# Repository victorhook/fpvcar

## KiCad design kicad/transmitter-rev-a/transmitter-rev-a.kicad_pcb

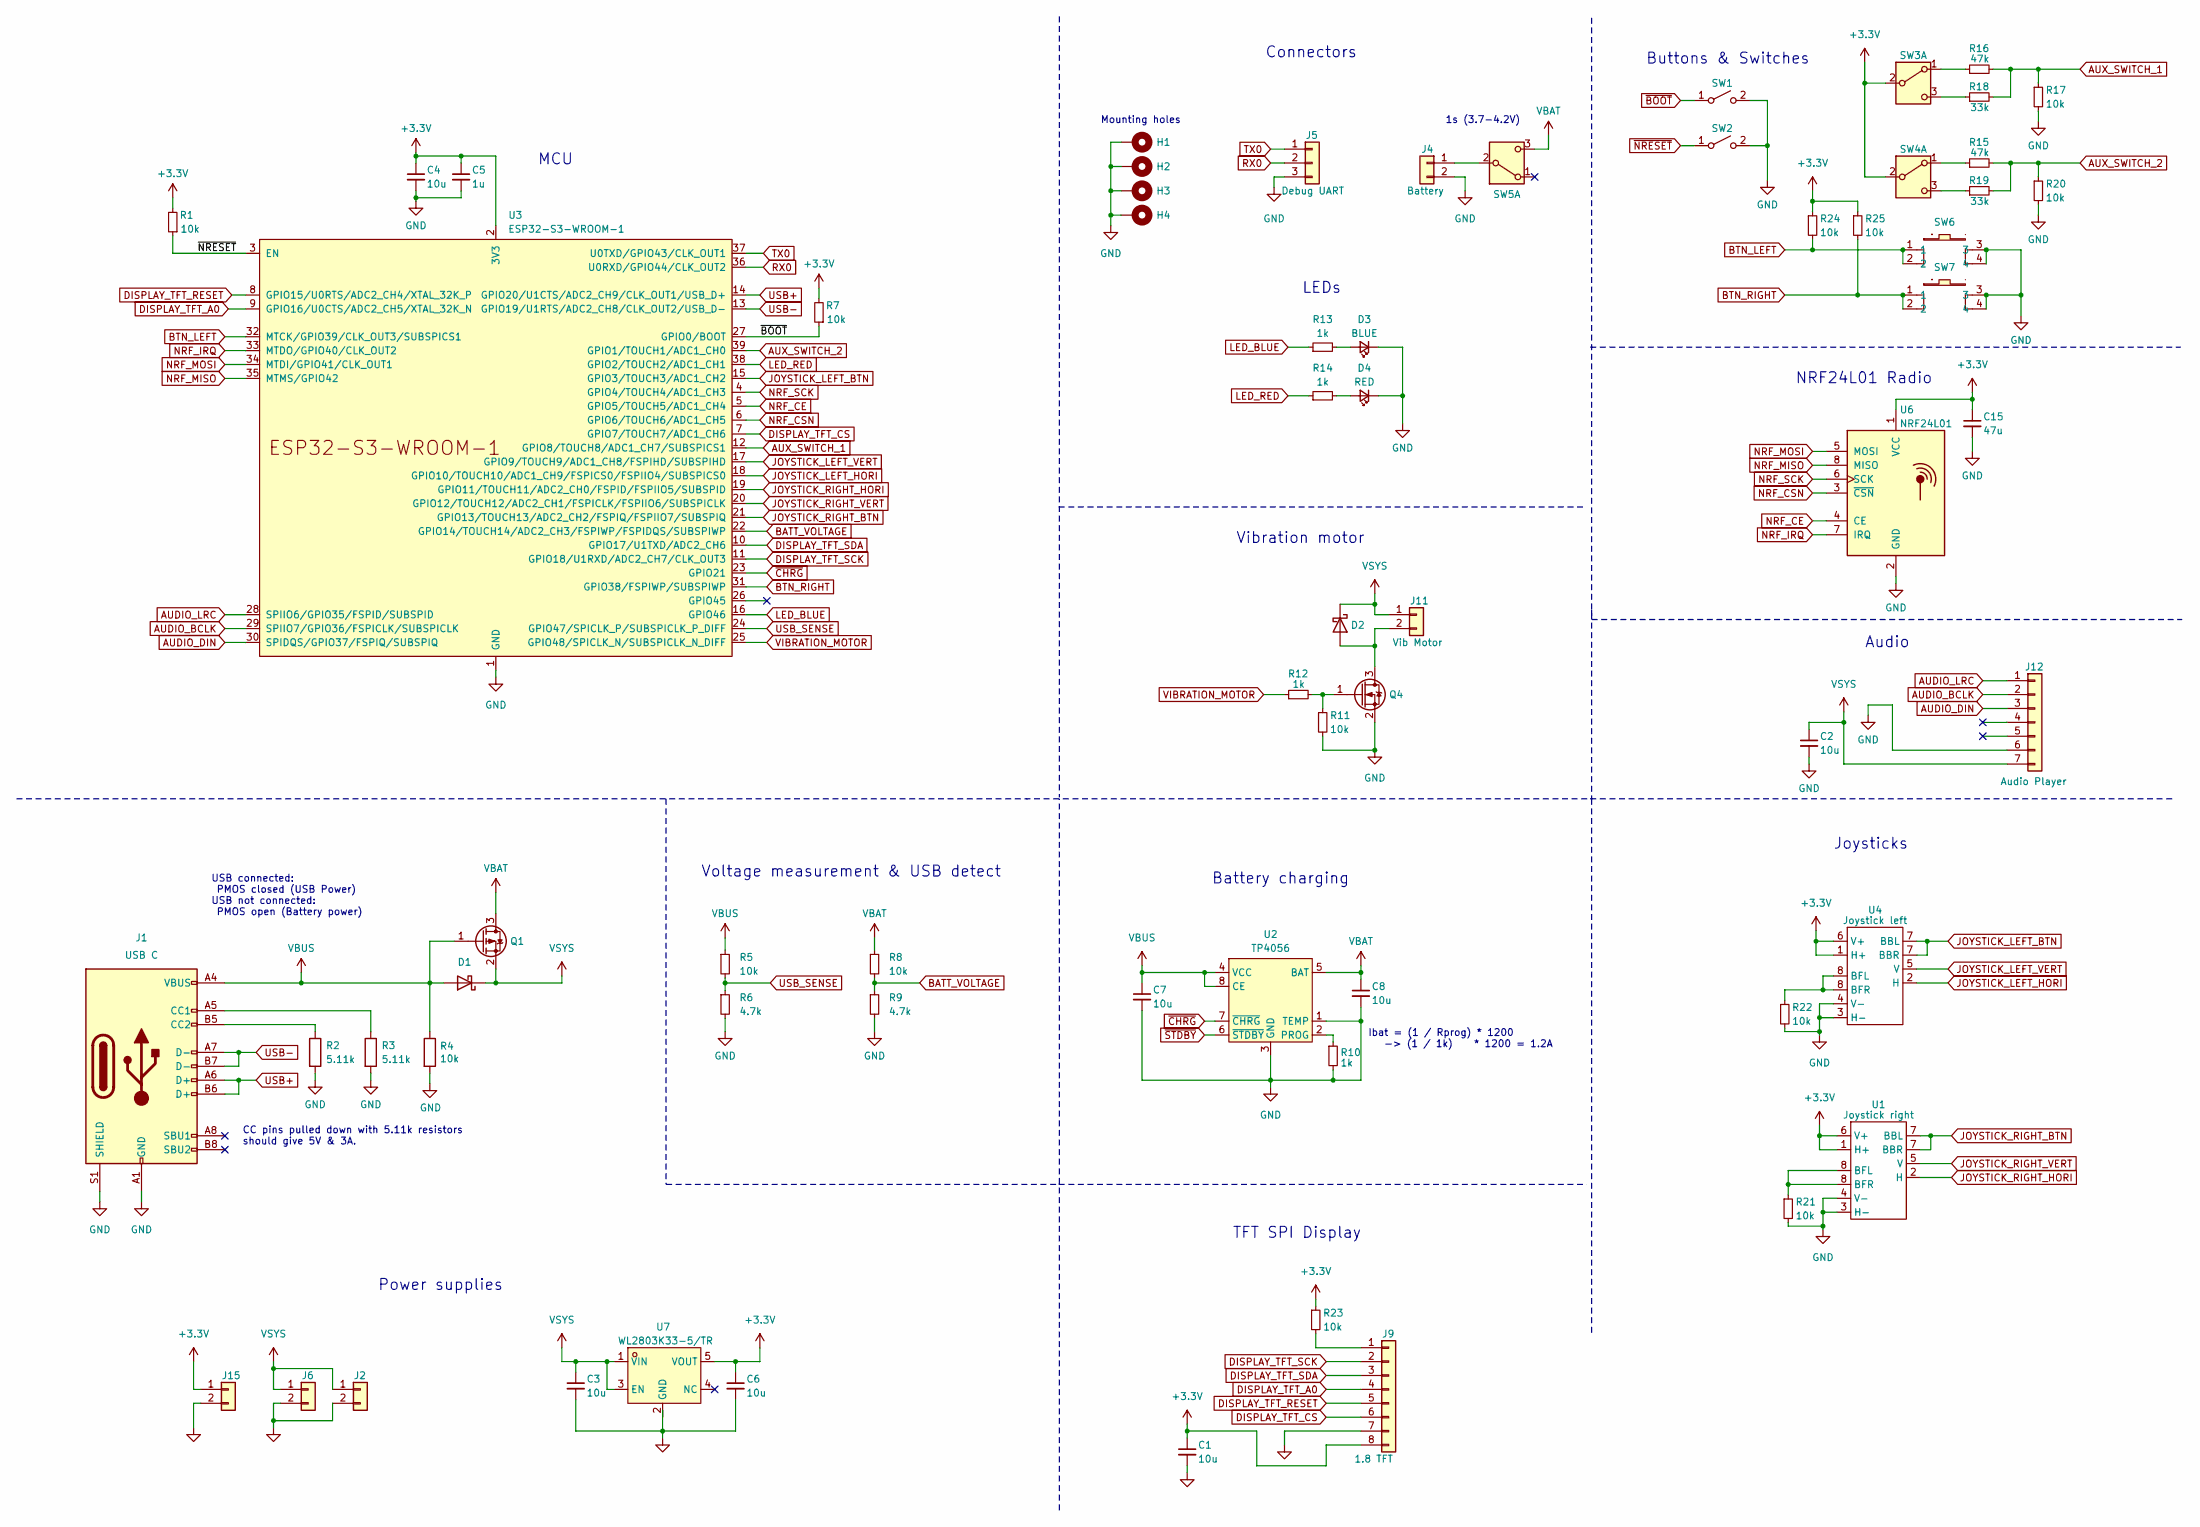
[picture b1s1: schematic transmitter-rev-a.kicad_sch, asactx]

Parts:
C1, C2, C3, C4, C6, C7, C8: 10u; C_0603_1608Metric
C5: 1u; C_0402_1005Metric
C15: 47u; C_1206_3216Metric
D1: D_Schottky; D_SOD-123
D2: D_Schottky; D_SOD-323
D3: BLUE; LED_0603_1608Metric
D4: RED; LED_0603_1608Metric
H1, H2, H3, H4: MountingHole_Pad; MountingHole_3.2mm_M3_Pad_Via
J1: USB C; USB-SMD_GT-USB-7010AN
J2, J6, J15: VSYS_VOLTAGE; Conn_01x02_no_Silk
J4: Battery; PinSocket_1x02_P2.54mm_Vertical
J5: Debug UART; PinSocket_1x03_P2.54mm_Vertical
J9: 1.8 TFT; PinSocket_1x08_P2.54mm_Vertical
J11: Vib Motor; Conn_01x02_no_Silk
J12: Audio Player; PinSocket_1x07_P2.54mm_Vertical
Q1: Q_PMOS_GSD; SOT-23
Q4: Q_NMOS_Depletion_GSD; SOT-23
R1, R4, R5, R7, R8, R11, R17, R20, R21, R22, R23, R24, R25: 10k; R_0402_1005Metric
R2, R3: 5.11k; R_0402_1005Metric
R6, R9: 4.7k; R_0402_1005Metric
R10, R12, R13, R14: 1k; R_0402_1005Metric
R15, R16: 47k; R_0402_1005Metric
R18, R19: 33k; R_0402_1005Metric
SW1, SW2: SW_SPST; SW-SMD_L4.0-W2.9-LS5.0
SW3: SWITCH 1; On-Off-On_Switch
SW4: SWITCH 2; On-Off-On_Switch
SW5: Battery; SideSwitch_5_Legs
SW6, SW7: KAN0641-0431B-L; KEY-SMD_4P-L6.0-W6.0-P4.50-LS10.0; LCSC Part C231670
U1: Joystick right; PS4tJoystick
U2: TP4056; ESOP-8_L4.9-W3.9-P1.27-LS6.0-BL-EP; LCSC Part C725790
U3: ESP32-S3-WROOM-1
U4: Joystick left; PS4tJoystick
U6: NRF24L01; PinSocket_2x04_P2.54mm_Vertical
U7: WL2803K33-5/TR; SOT-89-5; LCSC Part C192927

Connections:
+3.3V: C1.1, C4.1, C5.1, C6.1, C15.1, J9.8, J15.1, R1.2, R7.2, R23.1, R24.1, R25.1, SW3.2 (B), SW4.2 (B), U1.1 (H+), U1.6 (V+), U3.2 (3V3), U4.1 (H+), U4.6 (V+), U6.1 (VCC), U7.5 (VOUT)
AUDIO_BCLK: J12.2, U3.29 (SPIIO7/GPIO36/FSPICLK/SUBSPICLK)
AUDIO_DIN: J12.3, U3.30 (SPIDQS/GPIO37/FSPIQ/SUBSPIQ)
AUDIO_LRC: J12.1, U3.28 (SPIIO6/GPIO35/FSPID/SUBSPID)
AUX_SWITCH_1: R16.2, R17.1, R18.2, U3.12 (GPIO8/TOUCH8/ADC1_CH7/SUBSPICS1)
AUX_SWITCH_2: R15.2, R19.2, R20.1, U3.39 (GPIO1/TOUCH1/ADC1_CH0)
BATT_VOLTAGE: R8.2, R9.1, U3.22 (GPIO14/TOUCH14/ADC2_CH3/FSPIWP/FSPIDQS/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)
BTN_LEFT: R24.2, SW6.1, SW6.2, U3.32 (MTCK/GPIO39/CLK_OUT3/SUBSPICS1)
BTN_RIGHT: R25.2, SW7.1, SW7.2, U3.31 (GPIO38/FSPIWP/SUBSPIWP)
DISPLAY_TFT_A0: J9.4, U3.9 (GPIO16/U0CTS/ADC2_CH5/XTAL_32K_N)
DISPLAY_TFT_CS: J9.6, U3.7 (GPIO7/TOUCH7/ADC1_CH6)
DISPLAY_TFT_RESET: J9.5, U3.8 (GPIO15/U0RTS/ADC2_CH4/XTAL_32K_P)
DISPLAY_TFT_SCK: J9.2, U3.11 (GPIO18/U1RXD/ADC2_CH7/CLK_OUT3)
DISPLAY_TFT_SDA: J9.3, U3.10 (GPIO17/U1TXD/ADC2_CH6)
GND: C1.2, C2.2, C3.2, C4.2, C5.2, C6.2, C7.2, C8.2, C15.2, D3.1 (K), D4.1 (K), H1.1, H2.1, H3.1, H4.1, J1.A1 (GND), J1.A12 (GND), J1.B1 (GND), J1.B12 (GND), J1.S1 (SHIELD), J2.2, J4.2, J5.3, J6.2, J9.7, J12.6, J15.2, Q4.2 (S), R2.2, R3.2, R4.2, R6.2, R9.2, R10.2, R11.2, R17.2, R20.2, R21.2, R22.2, SW1.2 (B), SW2.2 (B), SW6.3, SW6.4, SW7.3, SW7.4, U1.3 (H-), U1.4 (V-), U2.1 (TEMP), U2.3 (GND), U3.1 (GND), U3.40 (GND), U3.41 (GND), U4.3 (H-), U4.4 (V-), U6.2 (GND)
JOYSTICK_LEFT_BTN: U3.15 (GPIO3/TOUCH3/ADC1_CH2), U4.7 (BBL)
JOYSTICK_LEFT_HORI: U3.18 (GPIO10/TOUCH10/ADC1_CH9/FSPICS0/FSPIIO4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), U4.2 (H)
JOYSTICK_LEFT_VERT: U3.17 (GPIO9/TOUCH9/ADC1_CH8/FSPIHD/SUBSPIHD), U4.5 (V)
JOYSTICK_RIGHT_BTN: U1.7 (BBL), U3.21 (GPIO13/TOUCH13/ADC2_CH2/FSPIQ/FSPIIO7/S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)
JOYSTICK_RIGHT_HORI: U1.2 (H), U3.19 (GPIO11/TOUCH11/ADC2_CH0/FSPID/FSPIIO5/S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)
JOYSTICK_RIGHT_VERT: U1.5 (V), U3.20 (GPIO12/TOUCH12/ADC2_CH1/FSPICLK/FSPIIO6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)
LED_BLUE: R13.1, U3.16 (GPIO46)
LED_RED: R14.1, U3.38 (GPIO2/TOUCH2/ADC1_CH1)
NRF_CE: U3.5 (GPIO5/TOUCH5/ADC1_CH4), U6.4 (CE)
NRF_CSN: U3.6 (GPIO6/TOUCH6/ADC1_CH5), U6.3 (~CSN)
NRF_IRQ: U3.33 (MTDO/GPIO40/CLK_OUT2), U6.7 (IRQ)
NRF_MISO: U3.35 (MTMS/GPIO42), U6.8 (MISO)
NRF_MOSI: U3.34 (MTDI/GPIO41/CLK_OUT1), U6.5 (MOSI)
NRF_SCK: U3.4 (GPIO4/TOUCH4/ADC1_CH3), U6.6 (SCK)
unnamed: D2.2 (A), J11.2, Q4.3 (D)
unnamed: D3.2 (A), R13.2
unnamed: D4.2 (A), R14.2
unnamed: J1.A5 (CC1), R3.1
unnamed: J1.B5 (CC2), R2.1
unnamed: J4.1, SW5.2 (B)
unnamed: J9.1, R23.2
unnamed: Q4.1 (G), R11.1, R12.2
unnamed: R16.1, SW3.1 (A)
unnamed: R18.1, SW3.3 (C)
unnamed: R15.1, SW4.1 (A)
unnamed: R19.1, SW4.3 (C)
unnamed: R21.1, U1.8 (BFL)
unnamed: R10.1, U2.2 (PROG)
unnamed: R22.1, U4.8 (BFL)
RX0: J5.2, U3.36 (U0RXD/GPIO44/CLK_OUT2)
TX0: J5.1, U3.37 (U0TXD/GPIO43/CLK_OUT1)
USB+: J1.A6 (D+), J1.B6 (D+), U3.14 (GPIO20/U1CTS/ADC2_CH9/CLK_OUT1/USB_D+)
USB-: J1.A7 (D-), J1.B7 (D-), U3.13 (GPIO19/U1RTS/ADC2_CH8/CLK_OUT2/USB_D-)
USB_SENSE: R5.2, R6.1, U3.24 (GPIO47/SPICLK_P/SUBSPICLK_P_DIFF)
VBAT: C8.1, Q1.3 (D), R8.1, SW5.3 (C), U2.5 (BAT)
VBUS: C7.1, D1.2 (A), J1.A4 (VBUS), J1.A9 (VBUS), J1.B4 (VBUS), J1.B9 (VBUS), Q1.1 (G), R4.1, R5.1, U2.4 (VCC), U2.8 (CE)
VIBRATION_MOTOR: R12.1, U3.25 (GPIO48/SPICLK_N/SUBSPICLK_N_DIFF)
VSYS: C2.1, C3.1, D1.1 (K), D2.1 (K), J2.1, J6.1, J11.1, J12.7, Q1.2 (S), U7.1 (VIN), U7.3 (EN)
~BOOT: R7.1, SW1.1 (A), U3.27 (GPIO0/BOOT)
~CHRG: U2.7 (~CHRG), U3.23 (GPIO21)
~NRESET: R1.1, SW2.1 (A), U3.3 (EN)
~STDBY: U2.6 (~STDBY)

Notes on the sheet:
Vibration motor
TFT SPI Display
MCU
Audio
LEDs
Ibat = (1 / Rprog) * 1200 -> (1 / 1k) * 1200 = 1.2A
NRF24L01 Radio
CC pins pulled down with 5.11k resistors should give 5V & 3A.
USB connected: PMOS closed (USB Power) USB not connected: PMOS open (Battery power)
Voltage measurement & USB detect
Connectors
Buttons & Switches
Joysticks
Power supplies
Battery charging
1s (3.7-4.2V)
Mounting holes

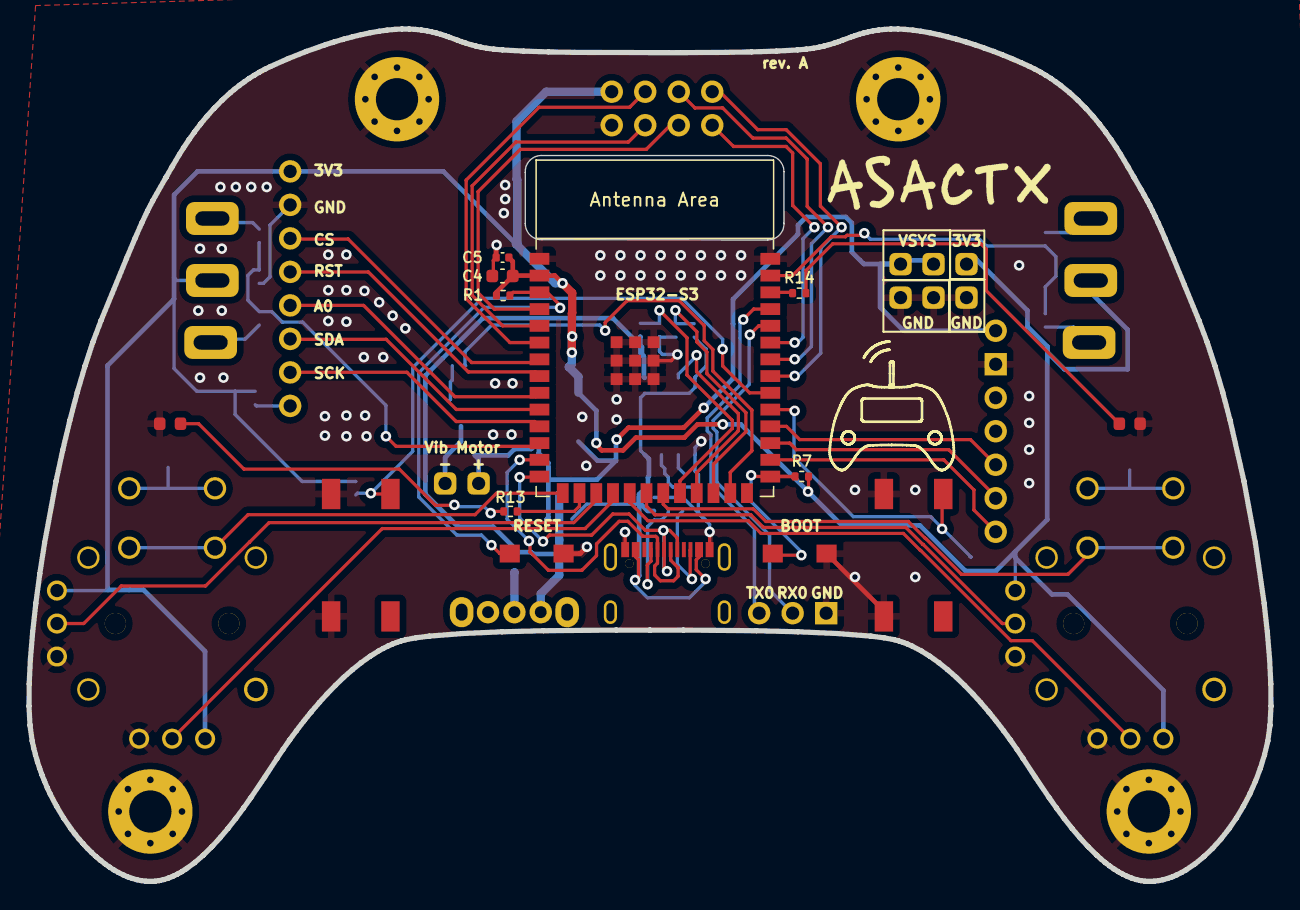
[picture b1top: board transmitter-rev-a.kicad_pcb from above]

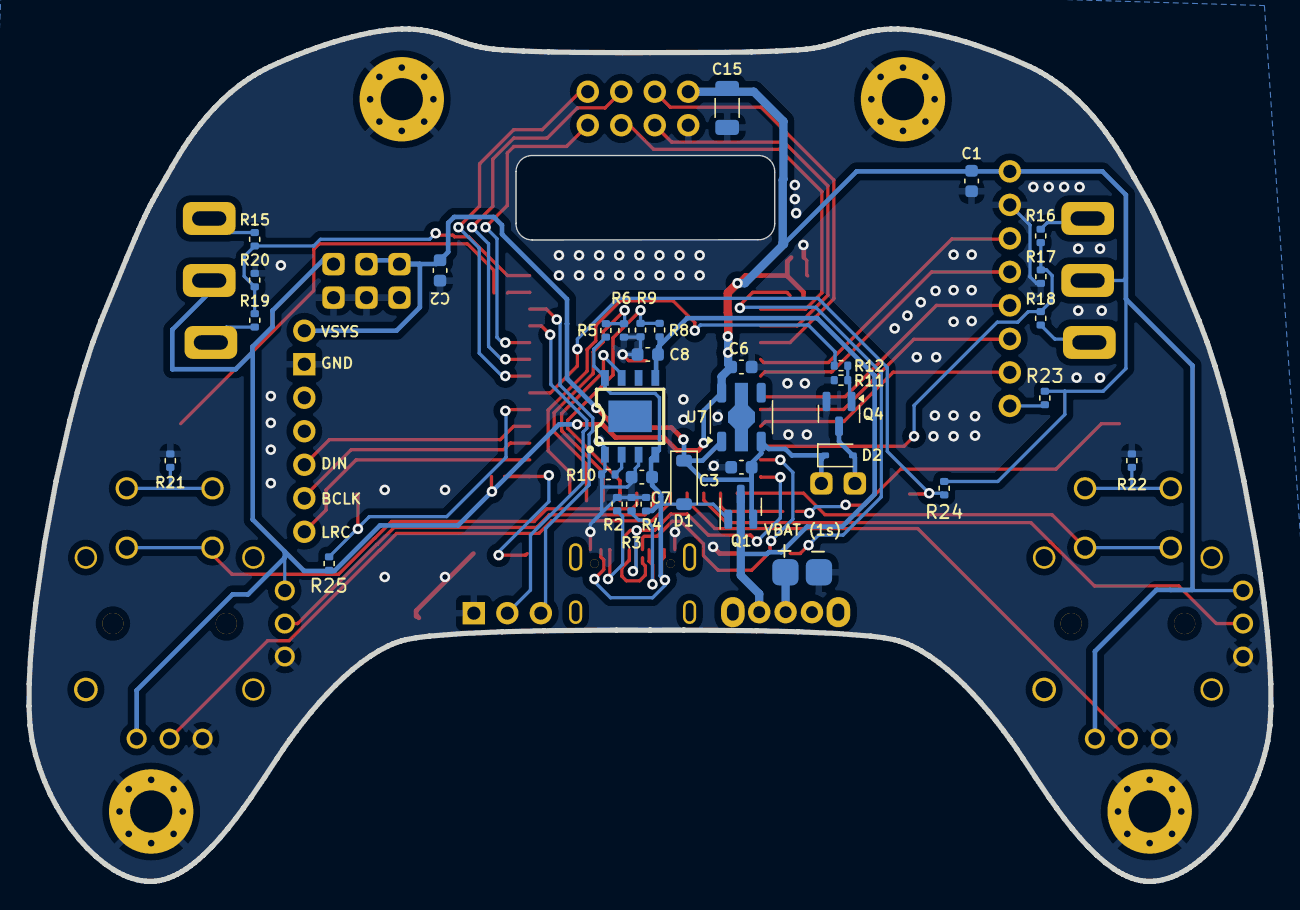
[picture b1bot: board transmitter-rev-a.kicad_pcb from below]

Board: 2 copper layers, 94.2 x 64.6 mm, 66 parts (35 on the bottom side), 56 nets.

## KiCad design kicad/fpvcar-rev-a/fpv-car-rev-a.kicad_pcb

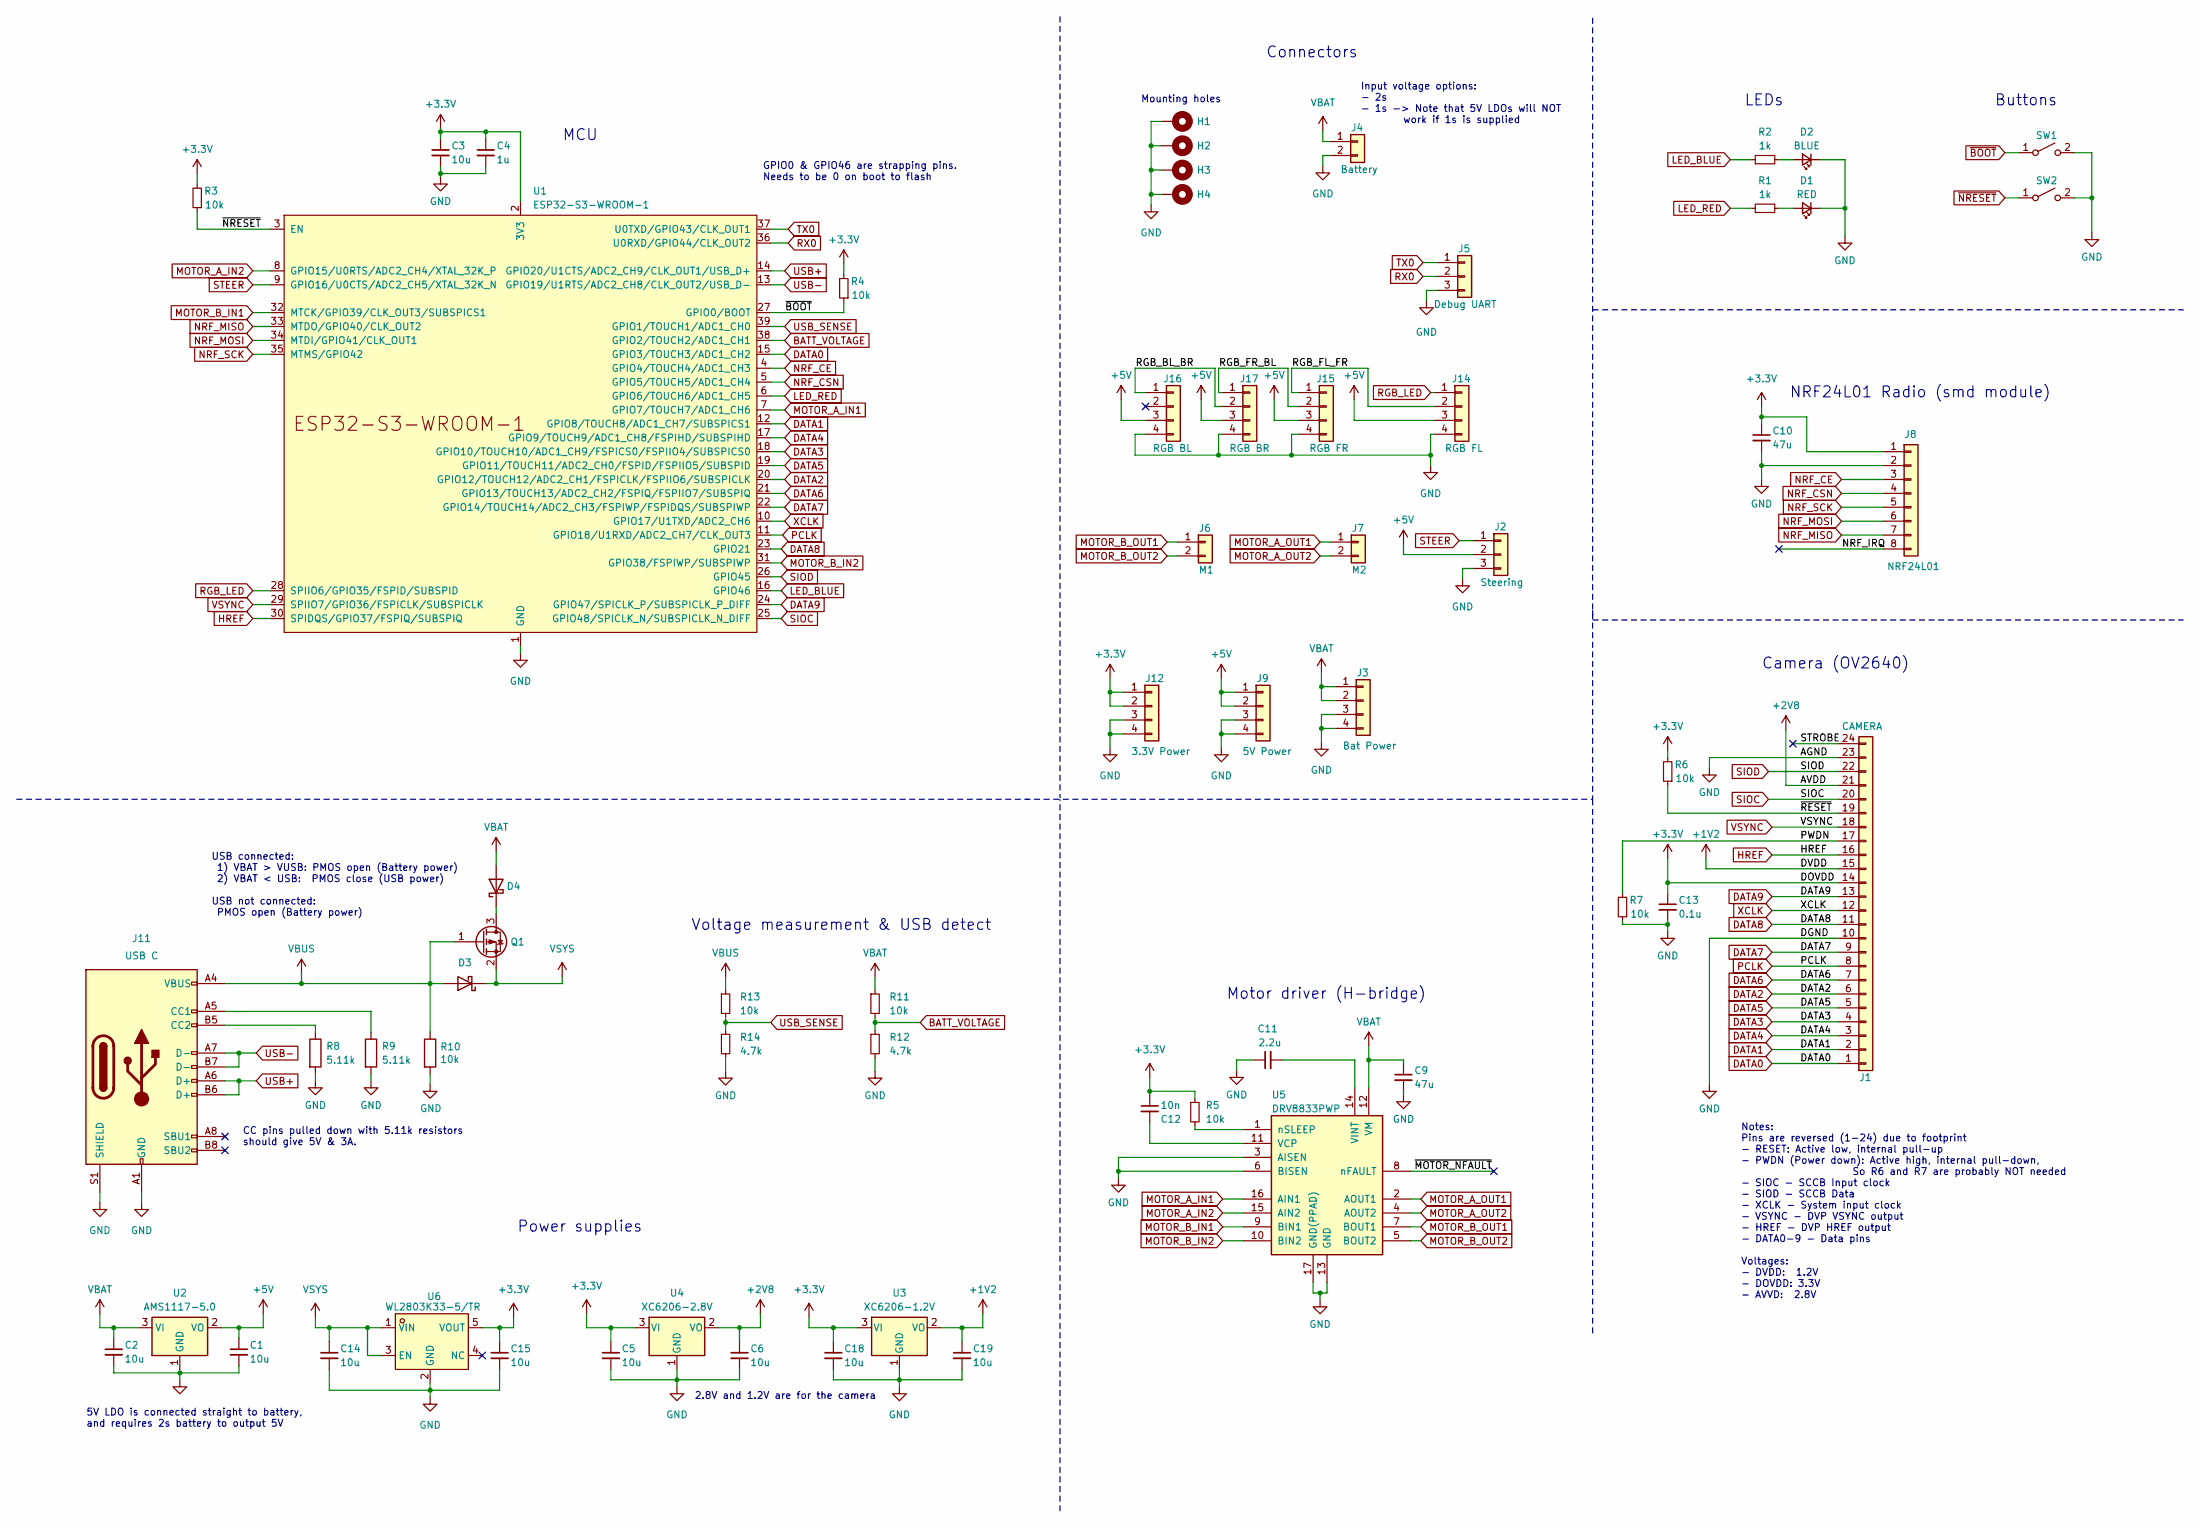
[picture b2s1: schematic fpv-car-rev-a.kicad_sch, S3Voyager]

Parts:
C1, C2, C3, C5, C6, C14, C15, C18, C19: 10u; C_0603_1608Metric
C4: 1u; C_0402_1005Metric
C9, C10: 47u; C_1206_3216Metric
C11: 2.2u; C_0402_1005Metric
C12: 10n; C_0402_1005Metric
C13: 0.1u; C_0402_1005Metric
D1: RED; LED_0603_1608Metric
D2: BLUE; LED_0603_1608Metric
D3: D_Schottky; D_SOD-123
D4: Schottky; D_SOD-123
H1, H2, H3, H4: MountingHole_Pad; MountingHole_2.2mm_M2_Pad_Via
J1: CAMERA; Hirose_FH12-24S-0.5SH_1x24-1MP_P0.50mm_Horizontal
J2: Steering; PinSocket_1x03_P2.54mm_Vertical
J3: Bat Power; conn_01x04
J4: Battery; PinSocket_1x02_P2.54mm_Vertical
J5: Debug UART; PinSocket_1x03_P2.54mm_Vertical
J6: M1; PinSocket_1x02_P2.54mm_Vertical
J7: M2; PinSocket_1x02_P2.54mm_Vertical
J8: NRF24L01; PinHeader_1x08_P1.27mm_Vertical
J9: 5V Power; conn_01x04
J11: USB C; USB-SMD_GT-USB-7010AN
J12: 3.3V Power; conn_01x04
J14: RGB FL; RGB_4_Pin_2mm_Female
J15: RGB FR; RGB_4_Pin_2mm_Female
J16: RGB BL; RGB_4_Pin_2mm_Female
J17: RGB BR; RGB_4_Pin_2mm_Female
Q1: Q_PMOS_GSD; SOT-23
R1, R2: 1k; R_0402_1005Metric
R3, R4, R5, R6, R7, R10, R11, R13: 10k; R_0402_1005Metric
R8, R9: 5.11k; R_0402_1005Metric
R12, R14: 4.7k; R_0402_1005Metric
SW1, SW2: SW_SPST; SW-SMD_L4.0-W2.9-LS5.0
U1: ESP32-S3-WROOM-1
U2: AMS1117-5.0; SOT-223-3_TabPin2
U3: XC6206-1.2V; SOT-23-3
U4: XC6206-2.8V; SOT-23-3
U5: DRV8833PWP; HTSSOP-16-1EP_4.4x5mm_P0.65mm_EP3.4x5mm_Mask2.46x2.31mm_The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
U6: WL2803K33-5/TR; SOT-89-5; LCSC Part C192927

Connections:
+1V2: C19.1, J1.15, U3.2 (VO)
+2V8: C6.1, J1.21, U4.2 (VO)
+3.3V: C3.1, C4.1, C5.1, C10.1, C12.1, C13.1, C15.1, C18.1, J1.14, J8.1, J12.1, J12.2, R3.2, R4.2, R5.1, R6.2, U1.2 (3V3), U3.3 (VI), U4.3 (VI), U6.5 (VOUT)
+5V: C1.1, J2.2, J9.1, J9.2, J14.3, J15.3, J16.3, J17.3, U2.2 (VO)
/NRF_IRQ: J8.8
/PWDN: J1.17, R7.2
/RGB_BL_BR: J16.1, J17.2
/RGB_FL_FR: J14.2, J15.1
/RGB_FR_BL: J15.2, J17.1
/STROBE: J1.24
/~MOTOR_NFAULT: U5.8 (nFAULT)
/~RESET: J1.19, R6.1
BATT_VOLTAGE: R11.2, R12.1, U1.38 (GPIO2/TOUCH2/ADC1_CH1)
DATA0: J1.1, U1.15 (GPIO3/TOUCH3/ADC1_CH2)
DATA1: J1.2, U1.12 (GPIO8/TOUCH8/ADC1_CH7/SUBSPICS1)
DATA2: J1.6, U1.20 (GPIO12/TOUCH12/ADC2_CH1/FSPICLK/FSPIIO6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)
DATA3: J1.4, U1.18 (GPIO10/TOUCH10/ADC1_CH9/FSPICS0/FSPIIO4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)
DATA4: J1.3, U1.17 (GPIO9/TOUCH9/ADC1_CH8/FSPIHD/SUBSPIHD)
DATA5: J1.5, U1.19 (GPIO11/TOUCH11/ADC2_CH0/FSPID/FSPIIO5/S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)
DATA6: J1.7, U1.21 (GPIO13/TOUCH13/ADC2_CH2/FSPIQ/FSPIIO7/S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)
DATA7: J1.9, U1.22 (GPIO14/TOUCH14/ADC2_CH3/FSPIWP/FSPIDQS/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)
DATA8: J1.11, U1.23 (GPIO21)
DATA9: J1.13, U1.24 (GPIO47/SPICLK_P/SUBSPICLK_P_DIFF)
GND: C1.2, C2.2, C3.2, C4.2, C5.2, C6.2, C9.2, C10.2, C11.1, C13.2, C14.2, C15.2, C18.2, C19.2, D1.1 (K), D2.1 (K), H1.1, H2.1, H3.1, H4.1, J1.10, J1.23, J2.3, J3.3, J3.4, J4.2, J5.3, J8.2, J9.3, J9.4, J11.A1 (GND), J11.A12 (GND), J11.B1 (GND), J11.B12 (GND), J11.S1 (SHIELD), J12.3, J12.4, J14.4, J15.4, J16.4, J17.4, R7.1, R8.2, R9.2, R10.2, R12.2, R14.2, SW1.2 (B), SW2.2 (B), U1.1 (GND), U1.40 (GND), U1.41 (GND), U2.1 (GND), U3.1 (GND), U4.1 (GND), U5.3 (AISEN), U5.6 (BISEN), U5.13 (GND), U5.17 (GND(PPAD)), U6.2 (GND)
HREF: J1.16, U1.30 (SPIDQS/GPIO37/FSPIQ/SUBSPIQ)
LED_BLUE: R2.1, U1.16 (GPIO46)
LED_RED: R1.1, U1.6 (GPIO6/TOUCH6/ADC1_CH5)
MOTOR_A_IN1: U1.7 (GPIO7/TOUCH7/ADC1_CH6), U5.16 (AIN1)
MOTOR_A_IN2: U1.8 (GPIO15/U0RTS/ADC2_CH4/XTAL_32K_P), U5.15 (AIN2)
MOTOR_A_OUT1: J7.1, U5.2 (AOUT1)
MOTOR_A_OUT2: J7.2, U5.4 (AOUT2)
MOTOR_B_IN1: U1.32 (MTCK/GPIO39/CLK_OUT3/SUBSPICS1), U5.9 (BIN1)
MOTOR_B_IN2: U1.31 (GPIO38/FSPIWP/SUBSPIWP), U5.10 (BIN2)
MOTOR_B_OUT1: J6.1, U5.7 (BOUT1)
MOTOR_B_OUT2: J6.2, U5.5 (BOUT2)
NRF_CE: J8.3, U1.4 (GPIO4/TOUCH4/ADC1_CH3)
NRF_CSN: J8.4, U1.5 (GPIO5/TOUCH5/ADC1_CH4)
NRF_MISO: J8.7, U1.33 (MTDO/GPIO40/CLK_OUT2)
NRF_MOSI: J8.6, U1.34 (MTDI/GPIO41/CLK_OUT1)
NRF_SCK: J8.5, U1.35 (MTMS/GPIO42)
unnamed: D1.2 (A), R1.2
unnamed: D2.2 (A), R2.2
unnamed: D4.1 (K), Q1.3 (D)
unnamed: J11.A5 (CC1), R9.1
unnamed: J11.B5 (CC2), R8.1
unnamed: C12.2, U5.11 (VCP)
unnamed: C11.2, U5.14 (VINT)
unnamed: R5.2, U5.1 (nSLEEP)
PCLK: J1.8, U1.11 (GPIO18/U1RXD/ADC2_CH7/CLK_OUT3)
RGB_LED: J14.1, U1.28 (SPIIO6/GPIO35/FSPID/SUBSPID)
RX0: J5.2, U1.36 (U0RXD/GPIO44/CLK_OUT2)
SIOC: J1.20, U1.25 (GPIO48/SPICLK_N/SUBSPICLK_N_DIFF)
SIOD: J1.22, U1.26 (GPIO45)
STEER: J2.1, U1.9 (GPIO16/U0CTS/ADC2_CH5/XTAL_32K_N)
TX0: J5.1, U1.37 (U0TXD/GPIO43/CLK_OUT1)
USB+: J11.A6 (D+), J11.B6 (D+), U1.14 (GPIO20/U1CTS/ADC2_CH9/CLK_OUT1/USB_D+)
USB-: J11.A7 (D-), J11.B7 (D-), U1.13 (GPIO19/U1RTS/ADC2_CH8/CLK_OUT2/USB_D-)
USB_SENSE: R13.2, R14.1, U1.39 (GPIO1/TOUCH1/ADC1_CH0)
VBAT: C2.1, C9.1, D4.2 (A), J3.1, J3.2, J4.1, R11.1, U2.3 (VI), U5.12 (VM)
VBUS: D3.2 (A), J11.A4 (VBUS), J11.A9 (VBUS), J11.B4 (VBUS), J11.B9 (VBUS), Q1.1 (G), R10.1, R13.1
VSYNC: J1.18, U1.29 (SPIIO7/GPIO36/FSPICLK/SUBSPICLK)
VSYS: C14.1, D3.1 (K), Q1.2 (S), U6.1 (VIN), U6.3 (EN)
XCLK: J1.12, U1.10 (GPIO17/U1TXD/ADC2_CH6)
~BOOT: R4.1, SW1.1 (A), U1.27 (GPIO0/BOOT)
~NRESET: R3.1, SW2.1 (A), U1.3 (EN)

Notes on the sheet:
Power supplies
Input voltage options: - 2s - 1s -> Note that 5V LDOs will NOT work if 1s is supplied
GPIO0 & GPIO46 are strapping pins. Needs to be 0 on boot to flash
Mounting holes
CC pins pulled down with 5.11k resistors should give 5V & 3A.
Buttons
LEDs
Motor driver (H-bridge)
MCU
Connectors
Camera (OV2640)
2.8V and 1.2V are for the camera
Notes: Pins are reversed (1-24) due to footprint - RESET: Active low, internal pull-up - PWDN (Power down): Active high, internal pull-down, So R6 and R7 are probably NOT needed - SIOC - SCCB Input clock - SIOD - SCCB Data - XCLK - System input clock - VSYNC - DVP VSYNC output - HREF - DVP HREF out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
NRF24L01 Radio (smd module)
Voltage measurement & USB detect
USB connected: 1) VBAT > VUSB: PMOS open (Battery power) 2) VBAT < USB: PMOS close (USB power) USB not connected: PMOS open (Battery power)
5V LDO is connected straight to battery, and requires 2s battery to output 5V

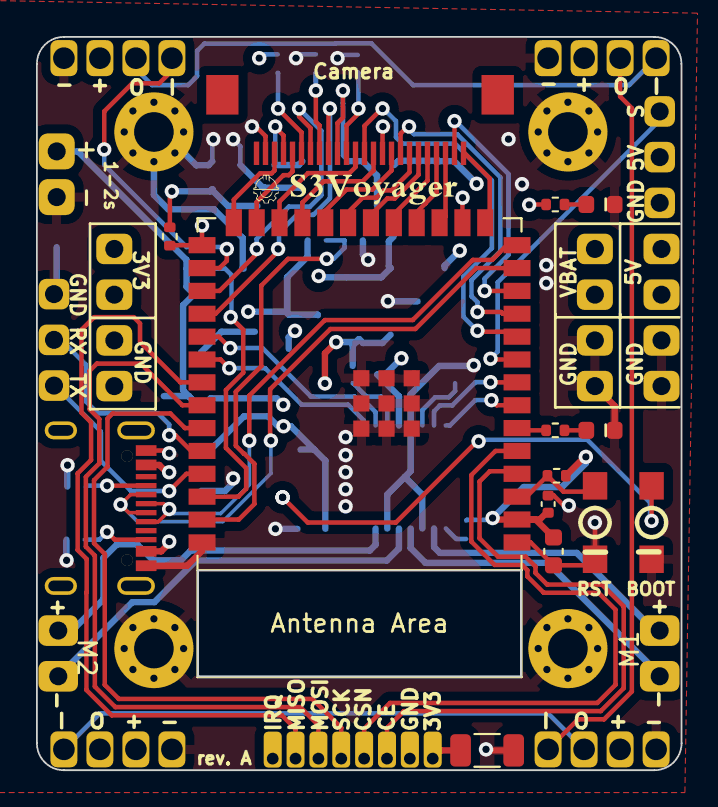
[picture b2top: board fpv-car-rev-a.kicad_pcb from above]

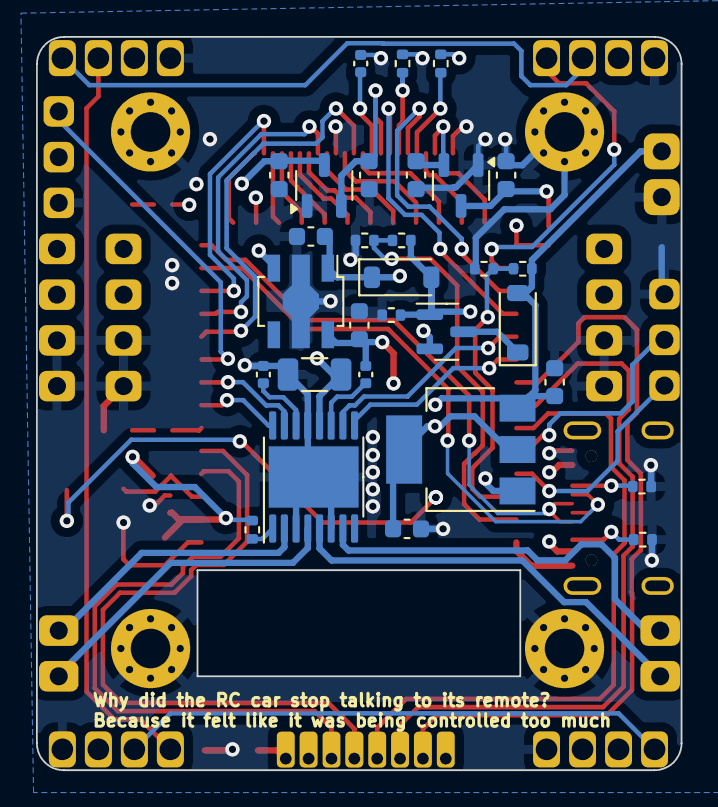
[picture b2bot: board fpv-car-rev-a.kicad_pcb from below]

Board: 4 copper layers, 35.8 x 40.7 mm, 61 parts (31 on the bottom side), 62 nets.

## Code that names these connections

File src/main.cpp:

#include <Arduino.h>
#include <WiFi.h>
#include <WiFiClient.h>

#define LOG_LOCAL_LEVEL ESP_LOG_VERBOSE
#include <esp_log.h>
#include <esp_system.h>
#include <nvs_flash.h>
#include <sys/param.h>
#include <string.h>

#include "freertos/FreeRTOS.h"
#include "freertos/task.h"

#include "esp_camera.h"

#include "credentials.h"

#define CAM_PIN_PWDN 32
#define CAM_PIN_RESET -1 //software reset will be performed
#define CAM_PIN_XCLK 0
#define CAM_PIN_SIOD 26
#define CAM_PIN_SIOC 27

#define CAM_PIN_D7 35
#define CAM_PIN_D6 34
#define CAM_PIN_D5 39
#define CAM_PIN_D4 36
#define CAM_PIN_D3 21
#define CAM_PIN_D2 19
#define CAM_PIN_D1 18
#define CAM_PIN_D0 5
#define CAM_PIN_VSYNC 25
#define CAM_PIN_HREF 23
#define CAM_PIN_PCLK 22

static const char *TAG = "example:take_picture";

static camera_config_t camera_config = {
    .pin_pwdn = CAM_PIN_PWDN,
    .pin_reset = CAM_PIN_RESET,
    .pin_xclk = CAM_PIN_XCLK,
    .pin_sccb_sda = CAM_PIN_SIOD,
    .pin_sccb_scl = CAM_PIN_SIOC,

    .pin_d7 = CAM_PIN_D7,
    .pin_d6 = CAM_PIN_D6,
    .pin_d5 = CAM_PIN_D5,
    .pin_d4 = CAM_PIN_D4,
    .pin_d3 = CAM_PIN_D3,
    .pin_d2 = CAM_PIN_D2,
    .pin_d1 = CAM_PIN_D1,
    .pin_d0 = CAM_PIN_D0,
    .pin_vsync = CAM_PIN_VSYNC,
    .pin_href = CAM_PIN_HREF,
    .pin_pclk = CAM_PIN_PCLK,

    //XCLK 20MHz or 10MHz for OV2640 double FPS (Experimental)
    .xclk_freq_hz = 20000000,
    .ledc_timer = LEDC_TIMER_0,
    .ledc_channel = LEDC_CHANNEL_0,

    .pixel_format = PIXFORMAT_RGB565, //YUV422,GRAYSCALE,RGB565,JPEG
    .frame_size = FRAMESIZE_QVGA,    //QQVGA-UXGA, For ESP32, do not use sizes above QVGA when not JPEG. The performance of the ESP32-S series has improved a lot, but JPEG mode always gives better frame rates.

    .jpeg_quality = 12, //0-63, for OV series camera sensors, lower number means higher quality
    .fb_count = 1,       //When jpeg mode is used, if fb_count more than one, the driver will work in continuous mode.
    .grab_mode = CAMERA_GRAB_WHEN_EMPTY,
};

static esp_err_t init_camera(void)
{
    //initialize the camera
    esp_err_t err = esp_camera_init(&camera_config);
    if (err != ESP_OK)
    {
        ESP_LOGE(TAG, "Camera Init Failed");
        return err;
    }

    return ESP_OK;
}

void setup()
{
    Serial.begin(115200);
    Serial.println("Initializing camera...");

    while(init_camera() != ESP_OK)
    {
        Serial.println("Failed to initialize camera!");
        delay(1000);
    }

    WiFi.begin(WIFI_SSID, WIFI_PASS);
    Serial.printf("Connecting to WiFi %s", WIFI_SSID);
    while(WiFi.status() != WL_CONNECTED)
    {
        Serial.print(".");
        delay(1000);
    }
    Serial.print("\n");

    Serial.println("Connected!");
}

#define TARGET_IP "192.168.10.113"
#define TARGET_PORT 8909
WiFiClient client;
WiFiUDP udp;
bool connected = false;

void loop()
{
    /*if (!client.connected())
    {
        Serial.printf("Connecting to: %s:%d\n", TARGET_IP, TARGET_PORT);
        connected = false;
        client.connect(TARGET_IP, TARGET_PORT);
    }
    else
    {
        if (!connected)
        {
            Serial.println("Connected to server!");
        }
        connected = true;
    }
    */

    //ESP_LOGI(TAG, "Taking picture...");
    camera_fb_t *pic = esp_camera_fb_get();

    //if (connected)
    {
        int i = 0;
        Serial.printf("Sending %d bytes to server\n", pic->len);
        udp.beginPacket(TARGET_IP, TARGET_PORT);
        udp.write(pic->buf, pic->len);
        udp.endPacket();
        /*
        while (i < pic->len)
        {
            int remaining_bytes = pic->len - i;
            int buf_size;
            if (remaining_bytes >= 1024)
            {
                buf_size = 1024;
            }
            else
            {
                buf_size = remaining_bytes;
            }
            i += buf_size;
        }*/
        Serial.println("Done!");
        //client.write("Hello world!\n");
        //client.flush();
    }

    // use pic->buf to access the image
    //ESP_LOGI(TAG, "Picture taken! Its size was: %zu bytes", pic->len);
    esp_camera_fb_return(pic);
    
    Serial.println(millis());
    //delay(1000);
}

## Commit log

2024-02-07 Initial testcode (for esp32cam) and some more improvements on schematic
2024-02-07 Schematic progress!
2024-02-09 More schematic improvements
2024-02-12 Swapped to OV2640 camera, started layout
2024-03-03 PCB for rev. A done!
    PCB name: S3Voyager :)
2024-03-25 Added initial transmitter cad
2024-03-26 Transmitter PCB progress
2024-05-01 Created platformio project for transmitter firmware
2024-05-01 Transmitter pcb progress. Schematic mostly done
2024-05-05 Transmitter PCB almost done in kicad
2024-05-06 Ordered PCBs for rev A
